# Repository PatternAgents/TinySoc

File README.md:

TinySoc
=============

PatternAgents TinySoc USB based Programmable System-on-Chip

[  
*PatternAgents TinySoc*](http://www.patternagents.com/projects/TinySoc.html)

PatternAgents TinySoc is a simple USB based Programmable System-on-Chip that you can either plug into a breadboard, 
or solder wires directly on to the board for embedded applications. 
PatternAgents TinySoc gives you several analog and digital channels that you can program.

Uses:

2 Channel analog audio mixer 

2 Channel analog audio filter 

USB to UART adaptor

USB to SPI adaptor

USB to I2C adaptor

USB data acquisition

You can read more about the PSoC1 Integrated Circuit used here : http://www.cypress.com/?id=177

This work is licensed under a Creative Commons Attribution-ShareAlike 4.0 International License
[  
*Licensing CC BY-SA 4.0*](http://creativecommons.org/licenses/by-sa/4.0/)

It may be used for Educational, Personal, or Commercial Use, provided you keep these notices,
attribution, and share-alike. When you apply these licenses to material you create, 
it meets the Freedom Defined definition of a "Free Cultural Work". 
Free cultural works are the ones that can be most readily used, shared, 
and remixed by others, and go furthest toward creating a commons of freely reusable materials.

-------------------------------------------------------------------------------------------

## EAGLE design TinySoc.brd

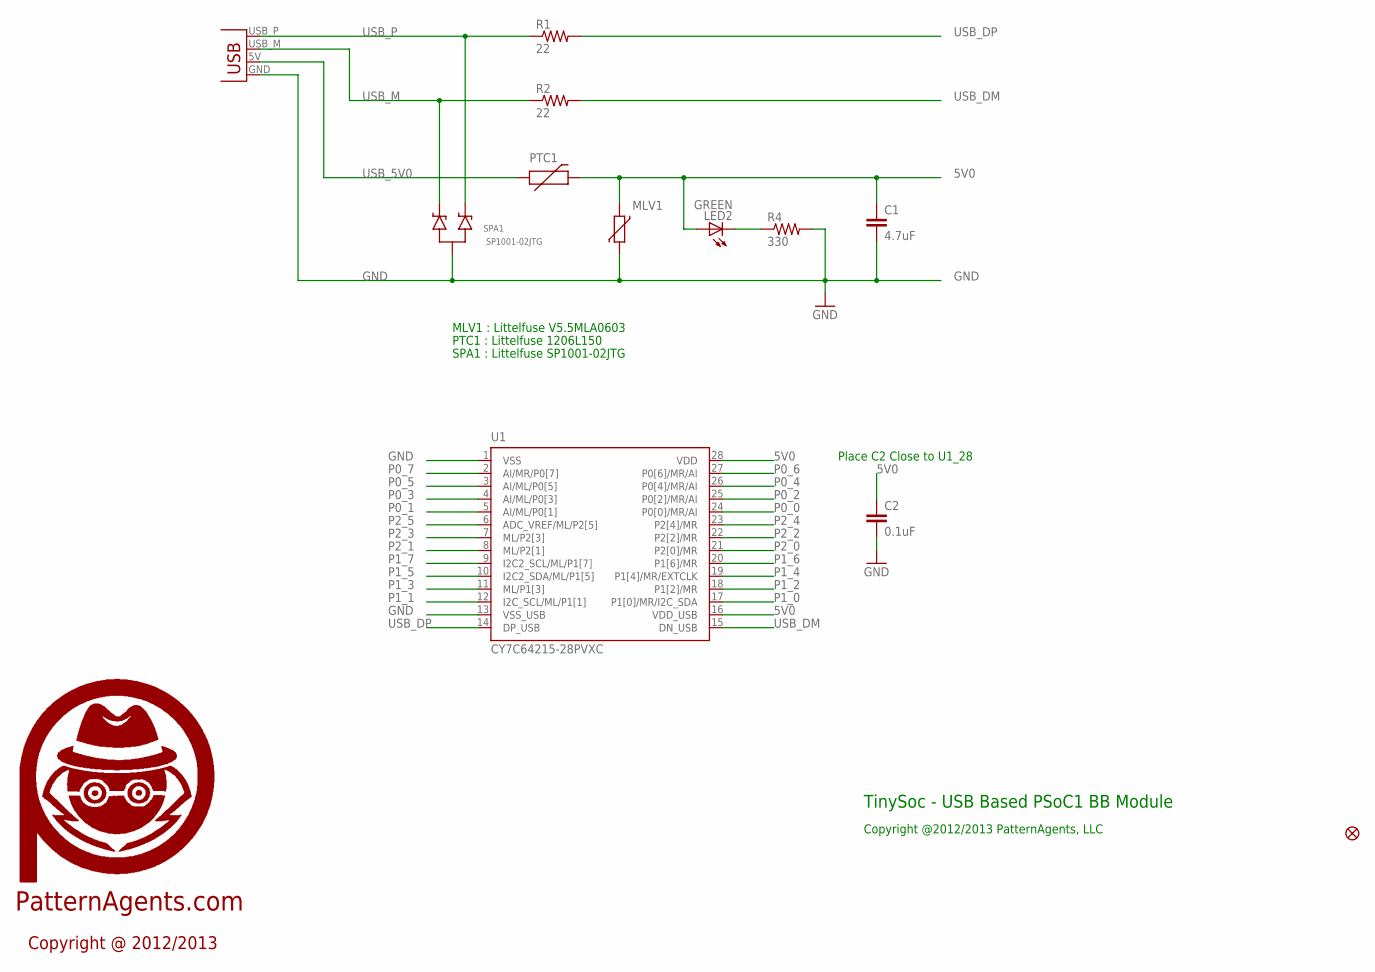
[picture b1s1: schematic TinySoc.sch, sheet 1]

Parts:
C1: 4.7uF; 0603-CAP
C2: 0.1uF; 0603-CAP
FID1: FIDUCIAL1.5X3; FIDUCIAL-1.5X3
LED2: GREEN; LED-0603
MLV1: VARISTORCN0603; CT/CN0603
PTC1: PTCSMD; PTC-1206
R1, R2: 22; 0603-RES
R4: 330; 0603-RES
SPA1: SP1001-02JTG; SC70-3
U1: CY7C64215-28PVXC; SSOP28
U$2: PA_LOGO_SYMSMALL; PA_LOGO_AGENT_SMALL_SYM
USBPCB: USBPCB; USB-A-PCB

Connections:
5V0: C1.1, C2.1, LED2.A, MLV1.1, PTC1.2, U1.16 (VDD_USB), U1.28 (VDD); also elsewhere on the board
GND: C1.2, C2.2, MLV1.2, R4.2, SPA1.3 (A), U1.1 (VSS), U1.13 (VSS_USB), USBPCB.GND; also elsewhere on the board
unnamed: LED2.C, R4.1
P0_0: U1.24 (P0[0]/MR/AI); also elsewhere on the board
P0_1: U1.5 (AI/ML/P0[1]); also elsewhere on the board
P0_2: U1.25 (P0[2]/MR/AI); also elsewhere on the board
P0_3: U1.4 (AI/ML/P0[3]); also elsewhere on the board
P0_4: U1.26 (P0[4]/MR/AI); also elsewhere on the board
P0_5: U1.3 (AI/ML/P0[5]); also elsewhere on the board
P0_6: U1.27 (P0[6]/MR/AI); also elsewhere on the board
P0_7: U1.2 (AI/MR/P0[7]); also elsewhere on the board
P1_0: U1.17 (P1[0]/MR/I2C_SDA); also elsewhere on the board
P1_1: U1.12 (I2C_SCL/ML/P1[1]); also elsewhere on the board
P1_2: U1.18 (P1[2]/MR); also elsewhere on the board
P1_3: U1.11 (ML/P1[3]); also elsewhere on the board
P1_4: U1.19 (P1[4]/MR/EXTCLK); also elsewhere on the board
P1_5: U1.10 (I2C2_SDA/ML/P1[5]); also elsewhere on the board
P1_6: U1.20 (P1[6]/MR); also elsewhere on the board
P1_7: U1.9 (I2C2_SCL/ML/P1[7]); also elsewhere on the board
P2_0: U1.21 (P2[0]/MR); also elsewhere on the board
P2_1: U1.8 (ML/P2[1]); also elsewhere on the board
P2_2: U1.22 (P2[2]/MR); also elsewhere on the board
P2_3: U1.7 (ML/P2[3]); also elsewhere on the board
P2_4: U1.23 (P2[4]/MR); also elsewhere on the board
P2_5: U1.6 (ADC_VREF/ML/P2[5]); also elsewhere on the board
USB_5V0: PTC1.1, USBPCB.5V (VBUS)
USB_DM: R2.2, U1.15 (DN_USB)
USB_DP: R1.2, U1.14 (DP_USB)
USB_M: R2.1, SPA1.2 (C2), USBPCB.USB_M (D-)
USB_P: R1.1, SPA1.1 (C1), USBPCB.USB_P (D+)

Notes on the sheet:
Place C2 Close to U1_28
MLV1 : Littelfuse V5.5MLA0603
PTC1 : Littelfuse 1206L150
SPA1 : Littelfuse SP1001-02JTG
PatternAgents.com
Copyright @ 2012/2013
TinySoc - USB Based PSoC1 BB Module
Copyright @2012/2013 PatternAgents, LLC

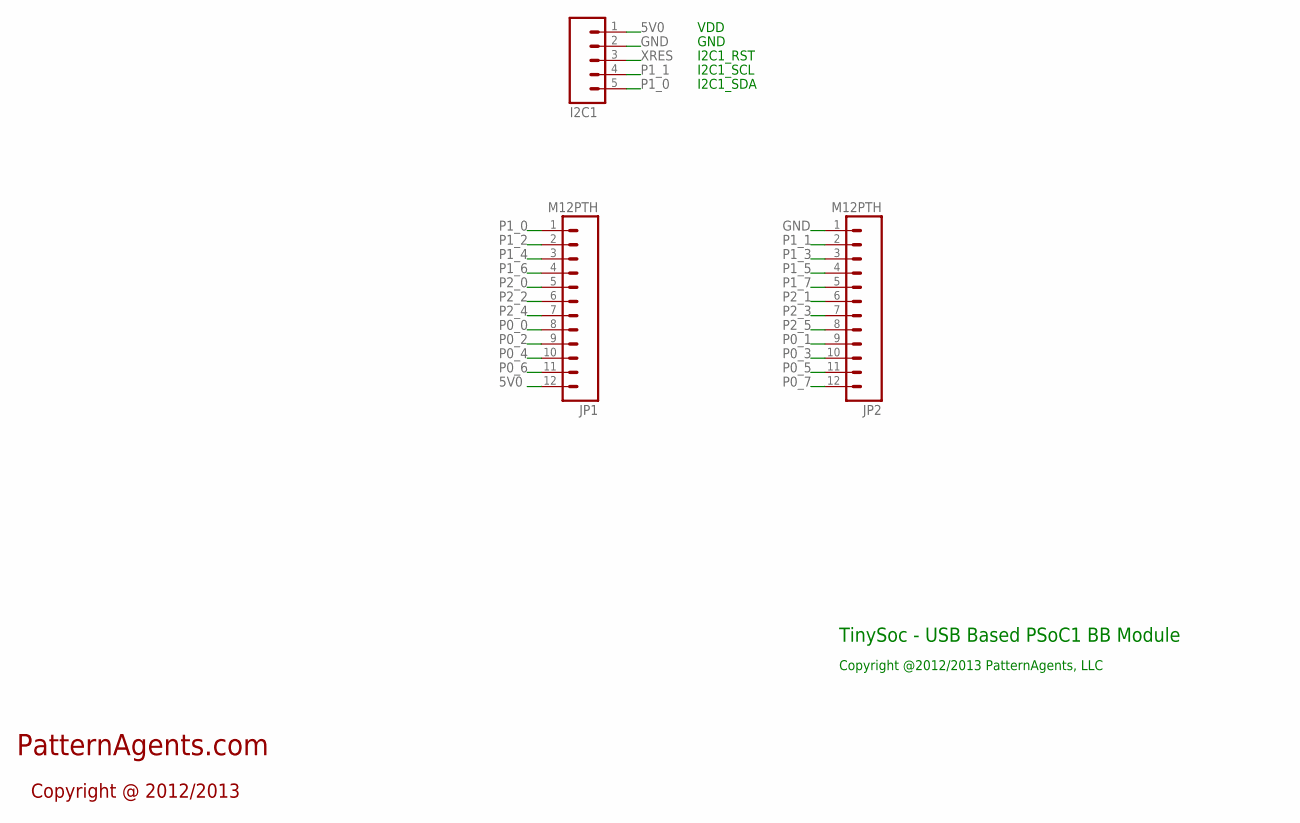
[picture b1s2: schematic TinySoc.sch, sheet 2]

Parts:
I2C1: M05PTH; 1X05
JP1, JP2: M12PTH; 1X12

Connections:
5V0: I2C1.1, JP1.12; also elsewhere on the board
GND: I2C1.2, JP2.1; also elsewhere on the board
P0_0: JP1.8; also elsewhere on the board
P0_1: JP2.9; also elsewhere on the board
P0_2: JP1.9; also elsewhere on the board
P0_3: JP2.10; also elsewhere on the board
P0_4: JP1.10; also elsewhere on the board
P0_5: JP2.11; also elsewhere on the board
P0_6: JP1.11; also elsewhere on the board
P0_7: JP2.12; also elsewhere on the board
P1_0: I2C1.5, JP1.1; also elsewhere on the board
P1_1: I2C1.4, JP2.2; also elsewhere on the board
P1_2: JP1.2; also elsewhere on the board
P1_3: JP2.3; also elsewhere on the board
P1_4: JP1.3; also elsewhere on the board
P1_5: JP2.4; also elsewhere on the board
P1_6: JP1.4; also elsewhere on the board
P1_7: JP2.5; also elsewhere on the board
P2_0: JP1.5; also elsewhere on the board
P2_1: JP2.6; also elsewhere on the board
P2_2: JP1.6; also elsewhere on the board
P2_3: JP2.7; also elsewhere on the board
P2_4: JP1.7; also elsewhere on the board
P2_5: JP2.8; also elsewhere on the board
XRES: I2C1.3

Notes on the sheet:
VDD
GND
I2C1_RST
I2C1_SCL
I2C1_SDA
TinySoc - USB Based PSoC1 BB Module
Copyright @2012/2013 PatternAgents, LLC
PatternAgents.com
Copyright @ 2012/2013

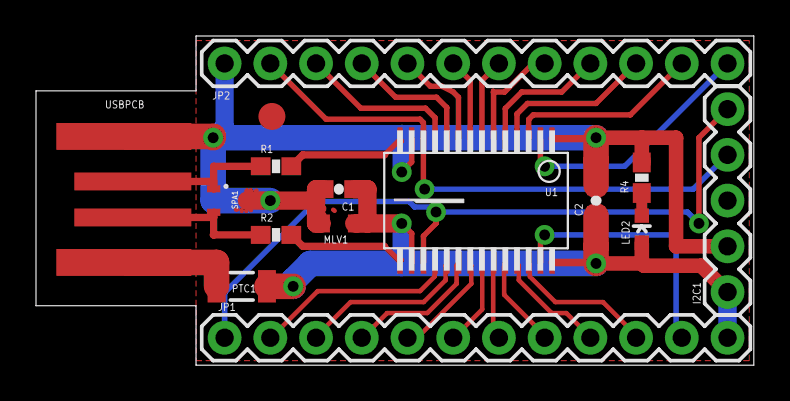
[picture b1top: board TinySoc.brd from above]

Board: 2 copper layers, 39.9 x 18.3 mm, 16 parts (1 on the bottom side), 30 nets.

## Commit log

2013-07-03 initial commit, project creation
2013-07-03 Added TinySoc Firmware example directory
2013-07-04 correct readme spacing
2013-07-15 fix image link
2013-07-18 Add GPLv3 license and normalize dual licensing
2013-07-18 link fixes
2013-07-19 fix links
2013-07-23 update images
2013-12-23 Move Licensing to CC 4.0 for consistancy
2014-01-05 Change legalcode.txt to "LICENSE" for consistancy

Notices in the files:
parts and their libraries:
PatternAgents-Logos: License : http://creativecommons.org/licenses/by-sa/3.0
(Creative Commons 3.0)
